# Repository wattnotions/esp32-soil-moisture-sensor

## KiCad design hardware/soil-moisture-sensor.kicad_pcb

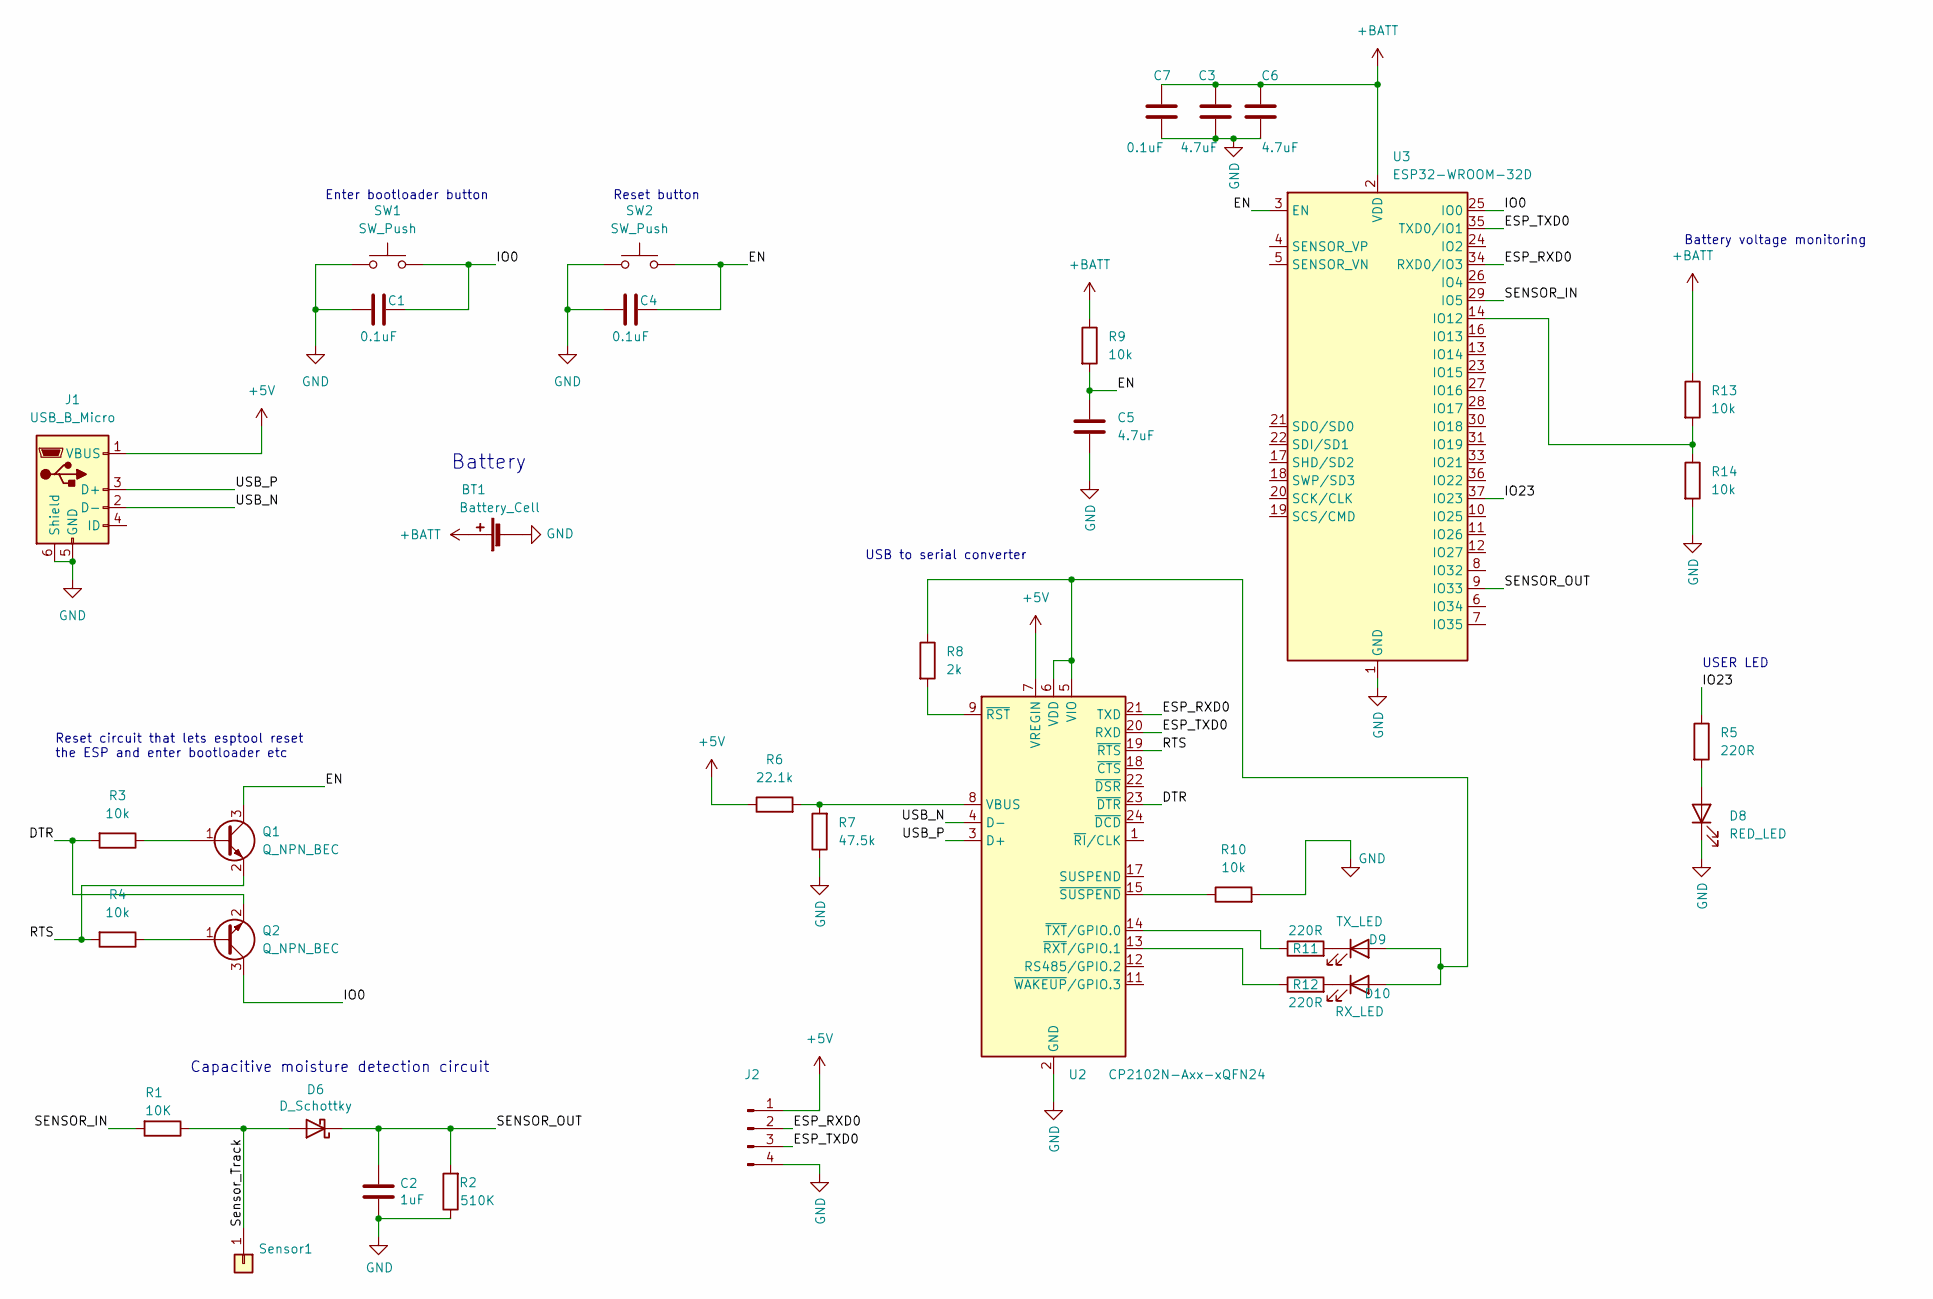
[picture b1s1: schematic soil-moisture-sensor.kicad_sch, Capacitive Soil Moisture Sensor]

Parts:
BT1: Battery_Cell; CR123A Battery Holder
C1, C4, C7: 0.1uF; C_0603_1608Metric; LCSC C694249
C2: 1uF; C_0603_1608Metric; LCSC C28323
C3, C5, C6: 4.7uF; C_0603_1608Metric; LCSC C108342
D6: D_Schottky; D_SOD-323_HandSoldering; LCSC C154819
D8: RED_LED; LED_0603_1608Metric; LCSC C118339
D9: TX_LED; LED_0603_1608Metric; LCSC C118339
D10: RX_LED; LED_0603_1608Metric; LCSC C118339
J1: USB_B_Micro; USB_Micro-B_Molex_47346-0001; LCSC C132560
J2: (no value)
Q1, Q2: Q_NPN_BEC; SOT-23; LCSC C164886
R1: 10K; R_0603_1608Metric; LCSC C17414
R2: 510K; R_0603_1608Metric; LCSC C17733
R3, R4, R9, R10, R13, R14: 10k; R_0603_1608Metric
R5: 220R; R_0603_1608Metric
R6: 22.1k; R_0603_1608Metric
R7: 47.5k; R_0603_1608Metric
R8: 2k; R_0603_1608Metric
R11, R12: 220R; R_0603_1608Metric; LCSC C365121
SW1, SW2: SW_Push; SW_SPST_B3U-1000P; LCSC C231329
Sensor1: Conn_01x01; Capacitive_Soil_Moisture_Sensor
U2: CP2102N-Axx-xQFN24; QFN-24-1EP_4x4mm_P0.5mm_EP2.6x2.6mm; LCSC C969151
U3: ESP32-WROOM-32D; ESP32-WROOM-32; LCSC C473012

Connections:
+5V: J1.1 (VBUS), J2.1, R6.1, U2.7 (VREGIN)
+BATT: BT1.1 (+), C3.1, C6.1, C7.1, R9.1, R13.1, U3.2 (VDD)
/DTR: Q2.2 (E), R3.2, U2.23 (~DTR)
/EN: C4.2, C5.1, Q1.3 (C), R9.2, SW2.2, U3.3 (EN)
/ESP_RXD0: J2.2, U2.21 (TXD), U3.34 (RXD0/IO3)
/ESP_TXD0: J2.3, U2.20 (RXD), U3.35 (TXD0/IO1)
/IO0: C1.2, Q2.3 (C), SW1.2, U3.25 (IO0)
/IO23: R5.1, U3.37 (IO23)
/RTS: Q1.2 (E), R4.2, U2.19 (~RTS)
/SENSOR_IN: R1.2, U3.29 (IO5)
/SENSOR_OUT: C2.1, D6.1 (K), R2.2, U3.9 (IO33)
/Sensor_Track: D6.2 (A), R1.1, Sensor1.1
/USB_N: J1.2 (D-), U2.4 (D-)
/USB_P: J1.3 (D+), U2.3 (D+)
GND: BT1.2 (-), C1.1, C2.2, C3.2, C4.1, C5.2, C6.2, C7.2, D8.1 (K), J1.5 (GND), J1.6 (Shield), J2.4, R2.1, R7.1, R10.2, R14.2, SW1.1, SW2.1, U2.2 (GND), U2.25 (GND), U3.1 (GND), U3.15 (GND), U3.38 (GND), U3.39 (GND)
unnamed: D8.2 (A), R5.2
unnamed: D9.1 (K), R11.2
unnamed: D10.1 (K), R12.2
unnamed: D9.2 (A), D10.2 (A), R8.1, U2.5 (VIO), U2.6 (VDD)
unnamed: Q1.1 (B), R3.1
unnamed: Q2.1 (B), R4.1
unnamed: R6.2, R7.2, U2.8 (VBUS)
unnamed: R8.2, U2.9 (~RST)
unnamed: R10.1, U2.15 (~SUSPEND)
unnamed: R11.1, U2.14 (~TXT/GPIO.0)
unnamed: R12.1, U2.13 (~RXT/GPIO.1)
unnamed: R13.2, R14.1, U3.14 (IO12)

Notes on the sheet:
USB to serial converter
USER LED
Reset circuit that lets esptool reset the ESP and enter bootloader etc
Battery voltage monitoring
Enter bootloader button
Battery
Capacitive moisture detection circuit
Reset button

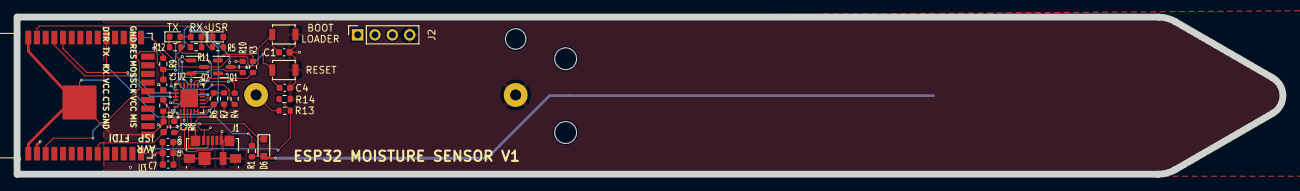
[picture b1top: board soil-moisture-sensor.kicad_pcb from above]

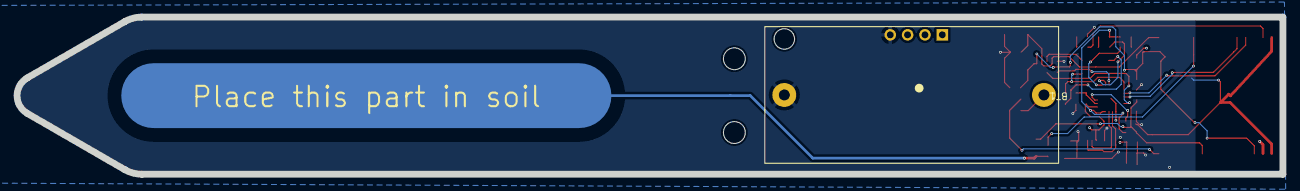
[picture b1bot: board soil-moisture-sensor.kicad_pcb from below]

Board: 4 copper layers, 185.3 x 23.0 mm, 35 parts (2 on the bottom side), 27 nets.

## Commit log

2022-06-05 started schematic
2022-06-07 schematic pretty much done
2022-06-07 changed power structure - removed ldo
2022-06-07 placement pretty much done
2022-06-09 updated cr123a fp
2022-06-11 layout finished
2022-06-15 removed esd diodes, changed sensor out to adc pin
2022-06-29 re-did a load of routing
2023-01-03 added bat mon circuit, made bat led a user led
2023-01-03 FIXED SOME DRC ERRORS
2023-01-03 added debug header and fixed more drc issues
2023-01-03 changed diode to one in stock on lcsc

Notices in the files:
hardware/soil-moisture-sensor.kicad_sch:
Licensed under CERN-OHL-P v2
